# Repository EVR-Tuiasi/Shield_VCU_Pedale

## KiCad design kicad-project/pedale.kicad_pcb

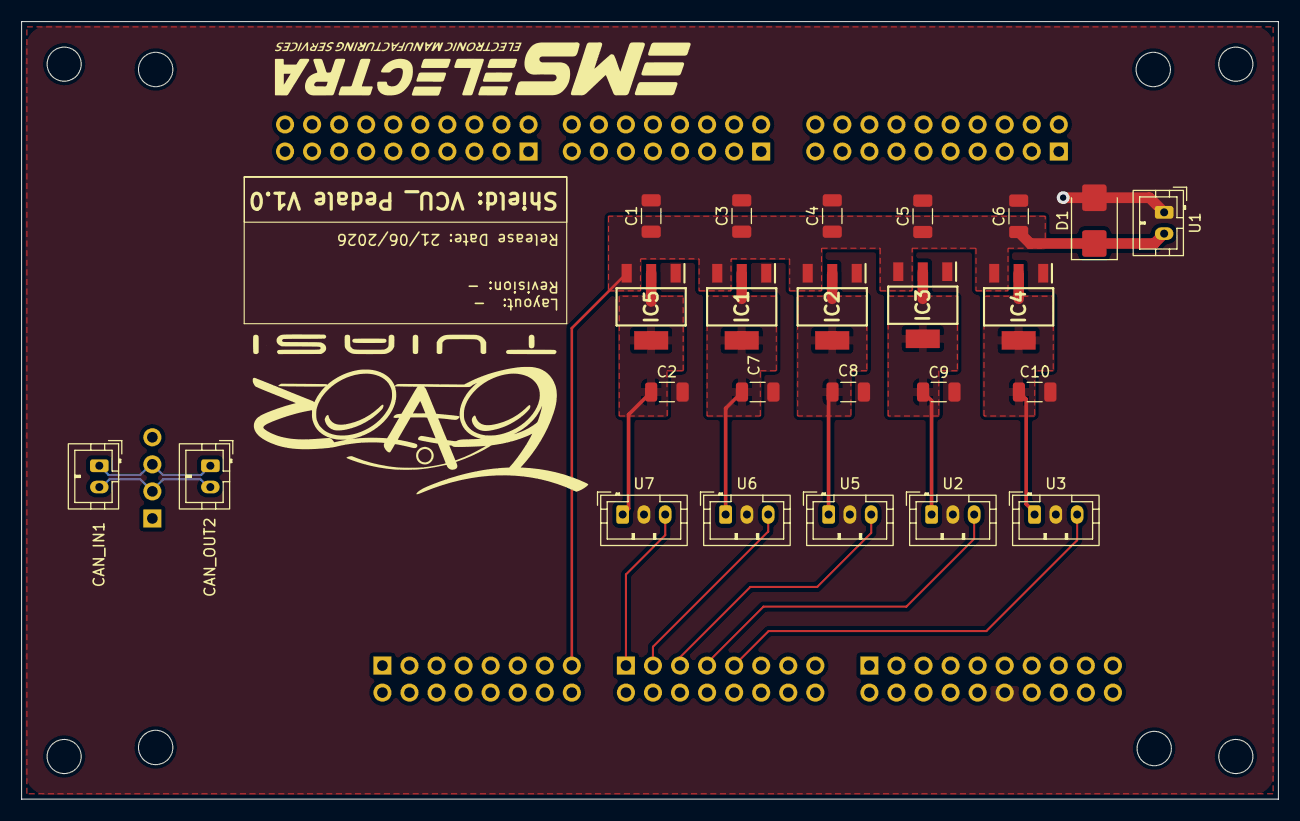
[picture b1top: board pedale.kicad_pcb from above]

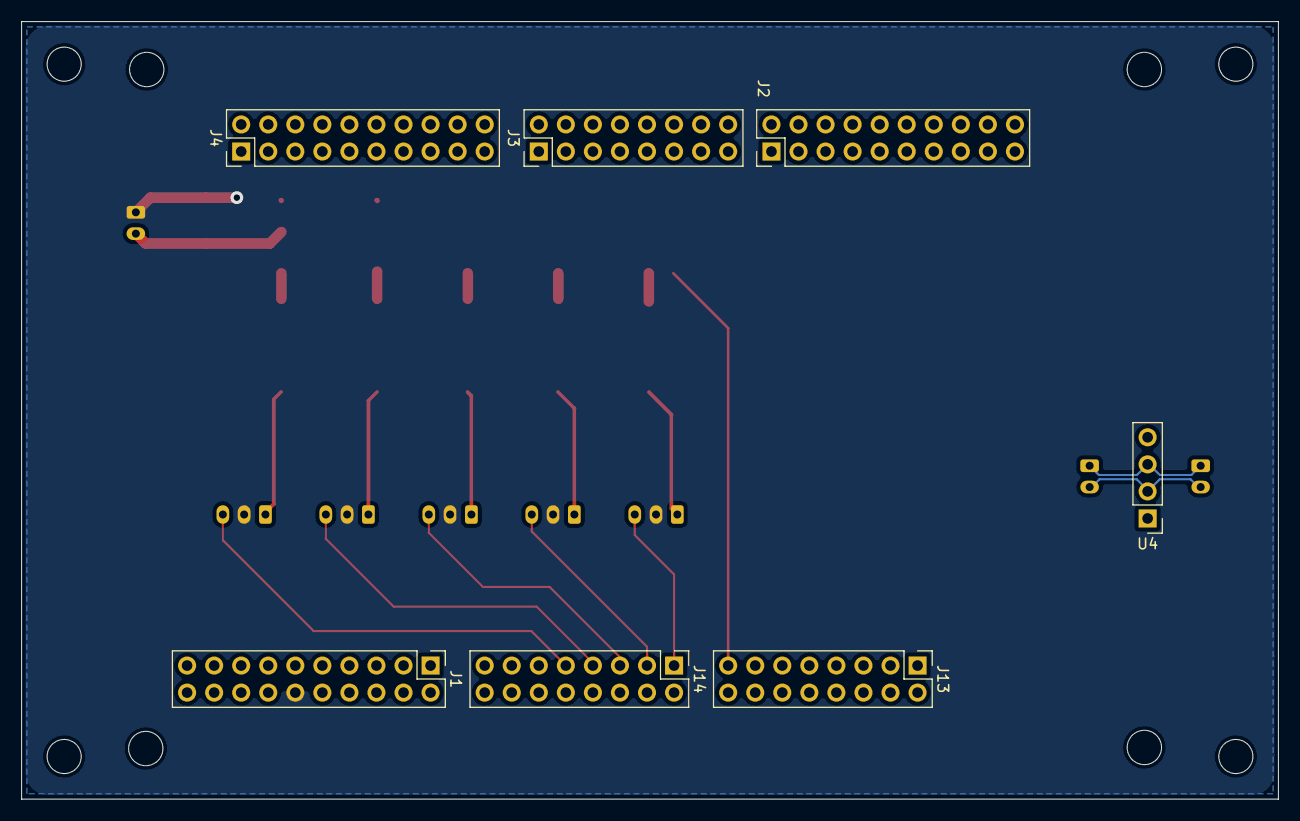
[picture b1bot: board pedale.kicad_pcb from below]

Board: 2 copper layers, 118.0 x 73.0 mm, 31 parts (7 on the bottom side), 14 nets.

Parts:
C1, C3, C4, C5, C6: 1μF; C_1206_3216Metric
C2, C7, C8, C9, C10: 2.2μF; C_1206_3216Metric
CAN_IN1: JST_PH_B2B-PH-K_1x02_P2.00mm_Vertical
CAN_OUT2: JST_PH_B2B-PH-K_1x02_P2.00mm_Vertical
D1: SS32; D_SMB
IC1, IC2, IC3, IC4, IC5: TLV76150DCYR; SOT230P700X180-4N
J1, J2, J4: PinHeader_2x10_P2.54mm_Vertical
J3, J13, J14: PinHeader_2x08_P2.54mm_Vertical
U1: JST_PH_B2B-PH-K_1x02_P2.00mm_Vertical
U2, U3, U5, U6, U7: JST_PH_B3B-PH-K_1x03_P2.00mm_Vertical
U4: PinHeader_1x04_P2.54mm_Vertical

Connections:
12V: C1.1, C3.1, C4.1, C5.1, C6.1, D1.1 (K), IC1.3 (IN), IC2.3 (IN), IC3.3 (IN), IC4.3 (IN), IC5.3 (IN), J13.15 (VBAT_15), U1.2 (12V)
/5V_1: C10.1, IC4.2 (OUT_1), IC4.4 (OUT_2), U3.1 (5V)
/5V_2: C9.1, IC3.2 (OUT_1), IC3.4 (OUT_2), U2.1 (5V)
/5V_3: C8.1, IC2.2 (OUT_1), IC2.4 (OUT_2), U5.1 (5V)
/5V_4: C7.1, IC1.2 (OUT_1), IC1.4 (OUT_2), U6.1 (5V)
/5V_5: C2.1, IC5.2 (OUT_1), IC5.4 (OUT_2), U7.1 (5V)
/CAN_N: CAN_IN1.2 (CANL), CAN_OUT2.2 (CANL), U4.2 (CANL)
/CAN_P: CAN_IN1.1 (CANH), CAN_OUT2.1 (CANH), U4.3 (CANH)
GND: C1.2, C2.2, C3.2, C4.2, C5.2, C6.2, C7.2, C8.2, C9.2, C10.2, D1.2 (A), IC1.1 (GND), IC2.1 (GND), IC3.1 (GND), IC4.1 (GND), IC5.1 (GND), J1.12 (GND_12), U1.1 (GND), U2.2 (GND), U3.2 (GND), U5.2 (GND), U6.2 (GND), U7.2 (GND)
unnamed: J14.7 (pta8), U2.3 (A0)
unnamed: J14.9 (pta9), U3.3 (A0)
unnamed: J14.5 (pta13), U5.3 (A0)
unnamed: J14.3 (ptd0), U6.3 (A0)
unnamed: J14.1 (ptd1), U7.3 (A0)

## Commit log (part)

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2026-03-18 Adaugat proiect kicad
2026-03-19 modificari
2026-03-22 modificari 2
2026-03-23 Schimbari dupa sugestii noi
2026-03-23 modificari aplicate
2026-03-24 modificari 3
2026-03-26 trebuie sa verific/schimb conectorii sa aiba pinii buni
2026-03-26 modificari 4
2026-03-26 viorel checked
2026-05-06 step file
2026-06-14 CAN_IN + CAN_OUT - added
2026-06-20 V_divirders removed+ Connectors moved
2026-06-20 GND on Diode placed
2026-06-21 Logos added (EMS/EVR)
2026-06-21 added exclude tracks area for diode
2026-06-21 Fix for unwanted GND connection
2026-06-21 Fixed 3 drc errors
2026-06-25 Fix one DRC warning for silkscreen
2026-06-26 Removed custom GND from supply connector
2026-06-29 GBR added
